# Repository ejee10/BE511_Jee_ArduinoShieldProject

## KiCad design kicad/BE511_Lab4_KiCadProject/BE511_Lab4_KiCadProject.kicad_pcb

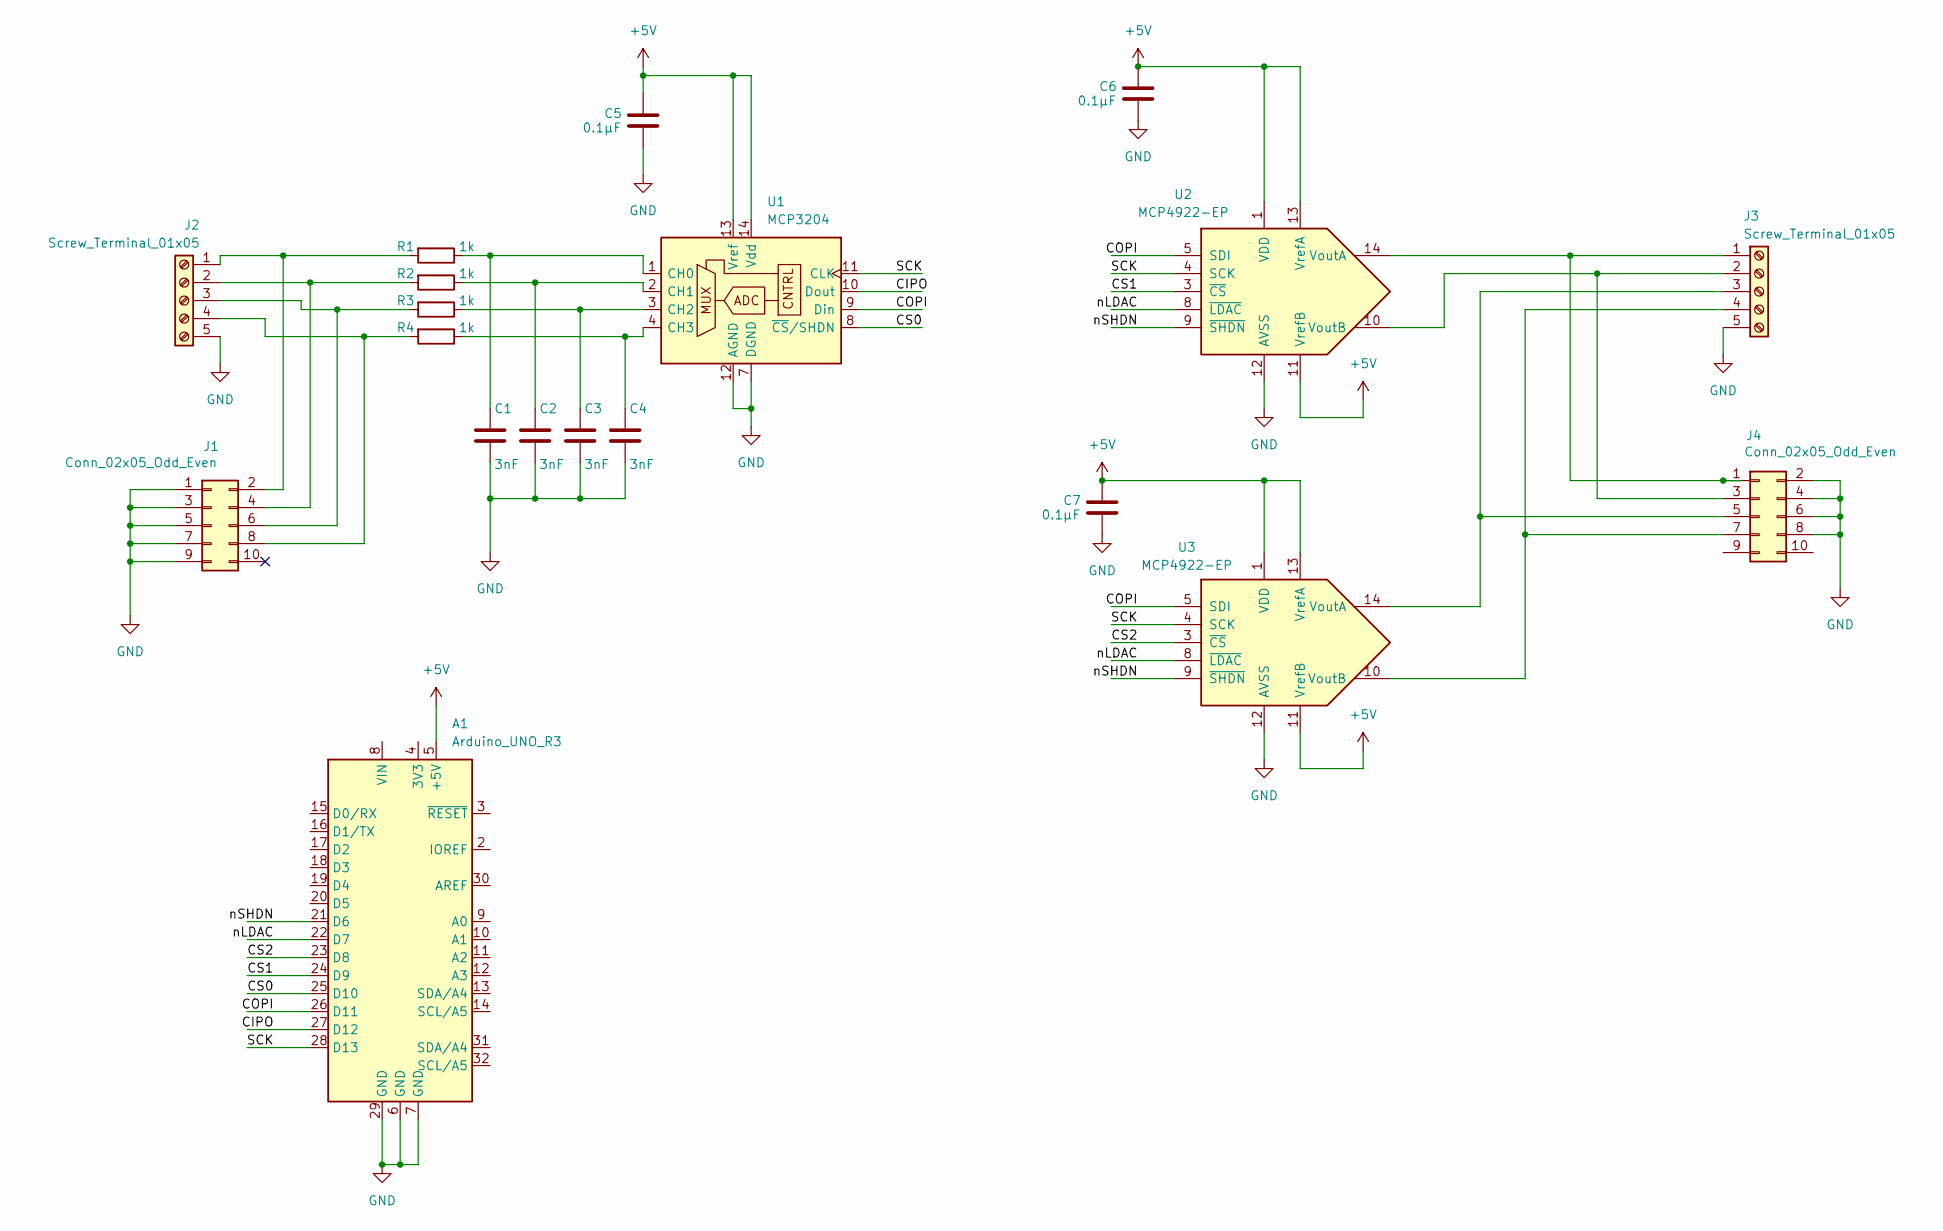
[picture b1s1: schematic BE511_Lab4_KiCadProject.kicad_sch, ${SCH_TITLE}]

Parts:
A1: Arduino_UNO_R3
C1, C2, C3, C4: 3nF; C_Disc_D4.7mm_W2.5mm_P5.00mm
C5, C6, C7: 0.1μF; C_Disc_D4.7mm_W2.5mm_P5.00mm
J1, J4: Conn_02x05_Odd_Even; PinSocket_2x05_P2.54mm_Vertical
J2, J3: Screw_Terminal_01x05; TerminalBlock_Xinya_XY308-2.54-5P_1x05_P2.54mm_Horizontal
R1, R2, R3, R4: 1k; R_Axial_DIN0207_L6.3mm_D2.5mm_P10.16mm_Horizontal
U1: MCP3204; DIP-14_W7.62mm
U2, U3: MCP4922-EP; DIP-14_W7.62mm

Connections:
+5V: A1.5 (+5V), C5.1, C6.1, C7.1, U1.13 (Vref), U1.14 (Vdd), U2.1 (VDD), U2.11 (VrefB), U2.13 (VrefA), U3.1 (VDD), U3.11 (VrefB), U3.13 (VrefA)
/CIPO: A1.27 (D12), U1.10 (Dout)
/COPI: A1.26 (D11), U1.9 (Din), U2.5 (SDI), U3.5 (SDI)
/CS0: A1.25 (D10), U1.8 (~CS/SHDN)
/CS1: A1.24 (D9), U2.3 (~CS)
/CS2: A1.23 (D8), U3.3 (~CS)
/SCK: A1.28 (D13), U1.11 (CLK), U2.4 (SCK), U3.4 (SCK)
/nLDAC: A1.22 (D7), U2.8 (~LDAC), U3.8 (~LDAC)
/nSHDN: A1.21 (D6), U2.9 (~SHDN), U3.9 (~SHDN)
GND: A1.6 (GND), A1.7 (GND), A1.29 (GND), C1.2, C2.2, C3.2, C4.2, C5.2, C6.2, C7.2, J1.1, J1.3, J1.5, J1.7, J1.9, J2.5, J3.5, J4.2, J4.4, J4.6, J4.8, U1.7 (DGND), U1.12 (AGND), U2.12 (AVSS), U3.12 (AVSS)
unnamed: J1.2, J2.1, R1.2
unnamed: J1.4, J2.2, R2.2
unnamed: J1.6, J2.3, R3.2
unnamed: J1.8, J2.4, R4.2
unnamed: J3.1, J4.1, U2.14 (VoutA)
unnamed: J3.2, J4.3, U2.10 (VoutB)
unnamed: J3.3, J4.5, U3.14 (VoutA)
unnamed: J3.4, J4.7, U3.10 (VoutB)
unnamed: C1.1, R1.1, U1.1 (CH0)
unnamed: C2.1, R2.1, U1.2 (CH1)
unnamed: C3.1, R3.1, U1.3 (CH2)
unnamed: C4.1, R4.1, U1.4 (CH3)

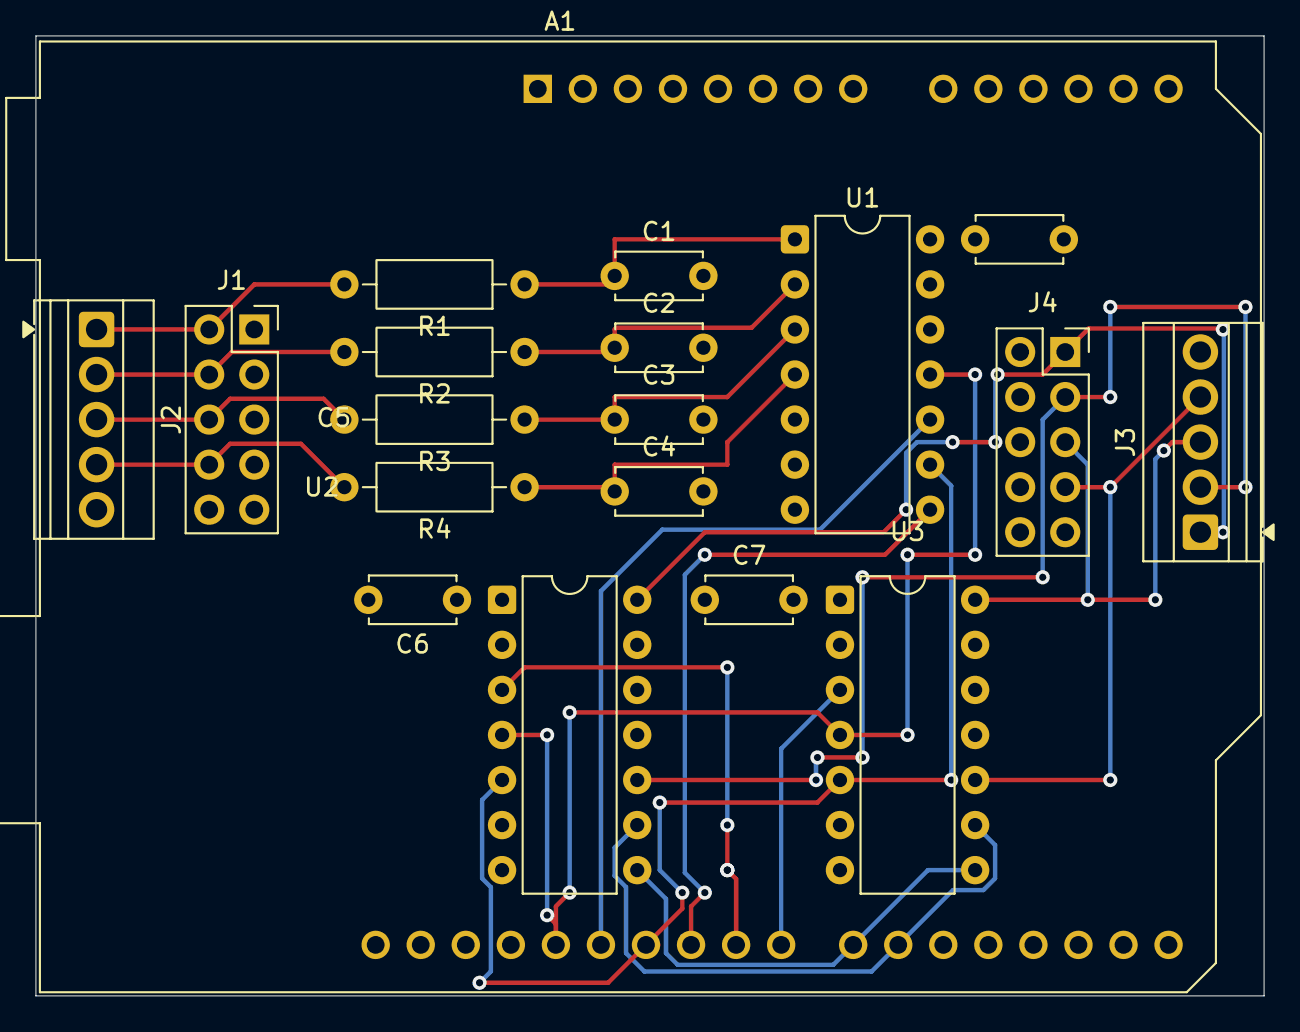
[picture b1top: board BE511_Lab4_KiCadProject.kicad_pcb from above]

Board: 4 copper layers, 69.2 x 54.1 mm, 19 parts (0 on the bottom side), 22 nets.
